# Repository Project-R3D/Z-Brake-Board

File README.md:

# Lulzbot Z Motor Automatic Brake

The [original design files](/Original_Lulz_Design/) contained within this repository were backed up from http://devel.lulzbot.com/electronics/dolores/ on Sept 8, 2021.
In case that gets taken down as well, please see this [archive.org](https://web.archive.org/web/20200216141835/http://devel.lulzbot.com/electronics/dolores/) backup as well.

This repository acts as a backup to that original design (which was sadly removed from all other Lulzbot servers) while complying with the original `CC BY SA 4.0` AND `GPL v3` license.

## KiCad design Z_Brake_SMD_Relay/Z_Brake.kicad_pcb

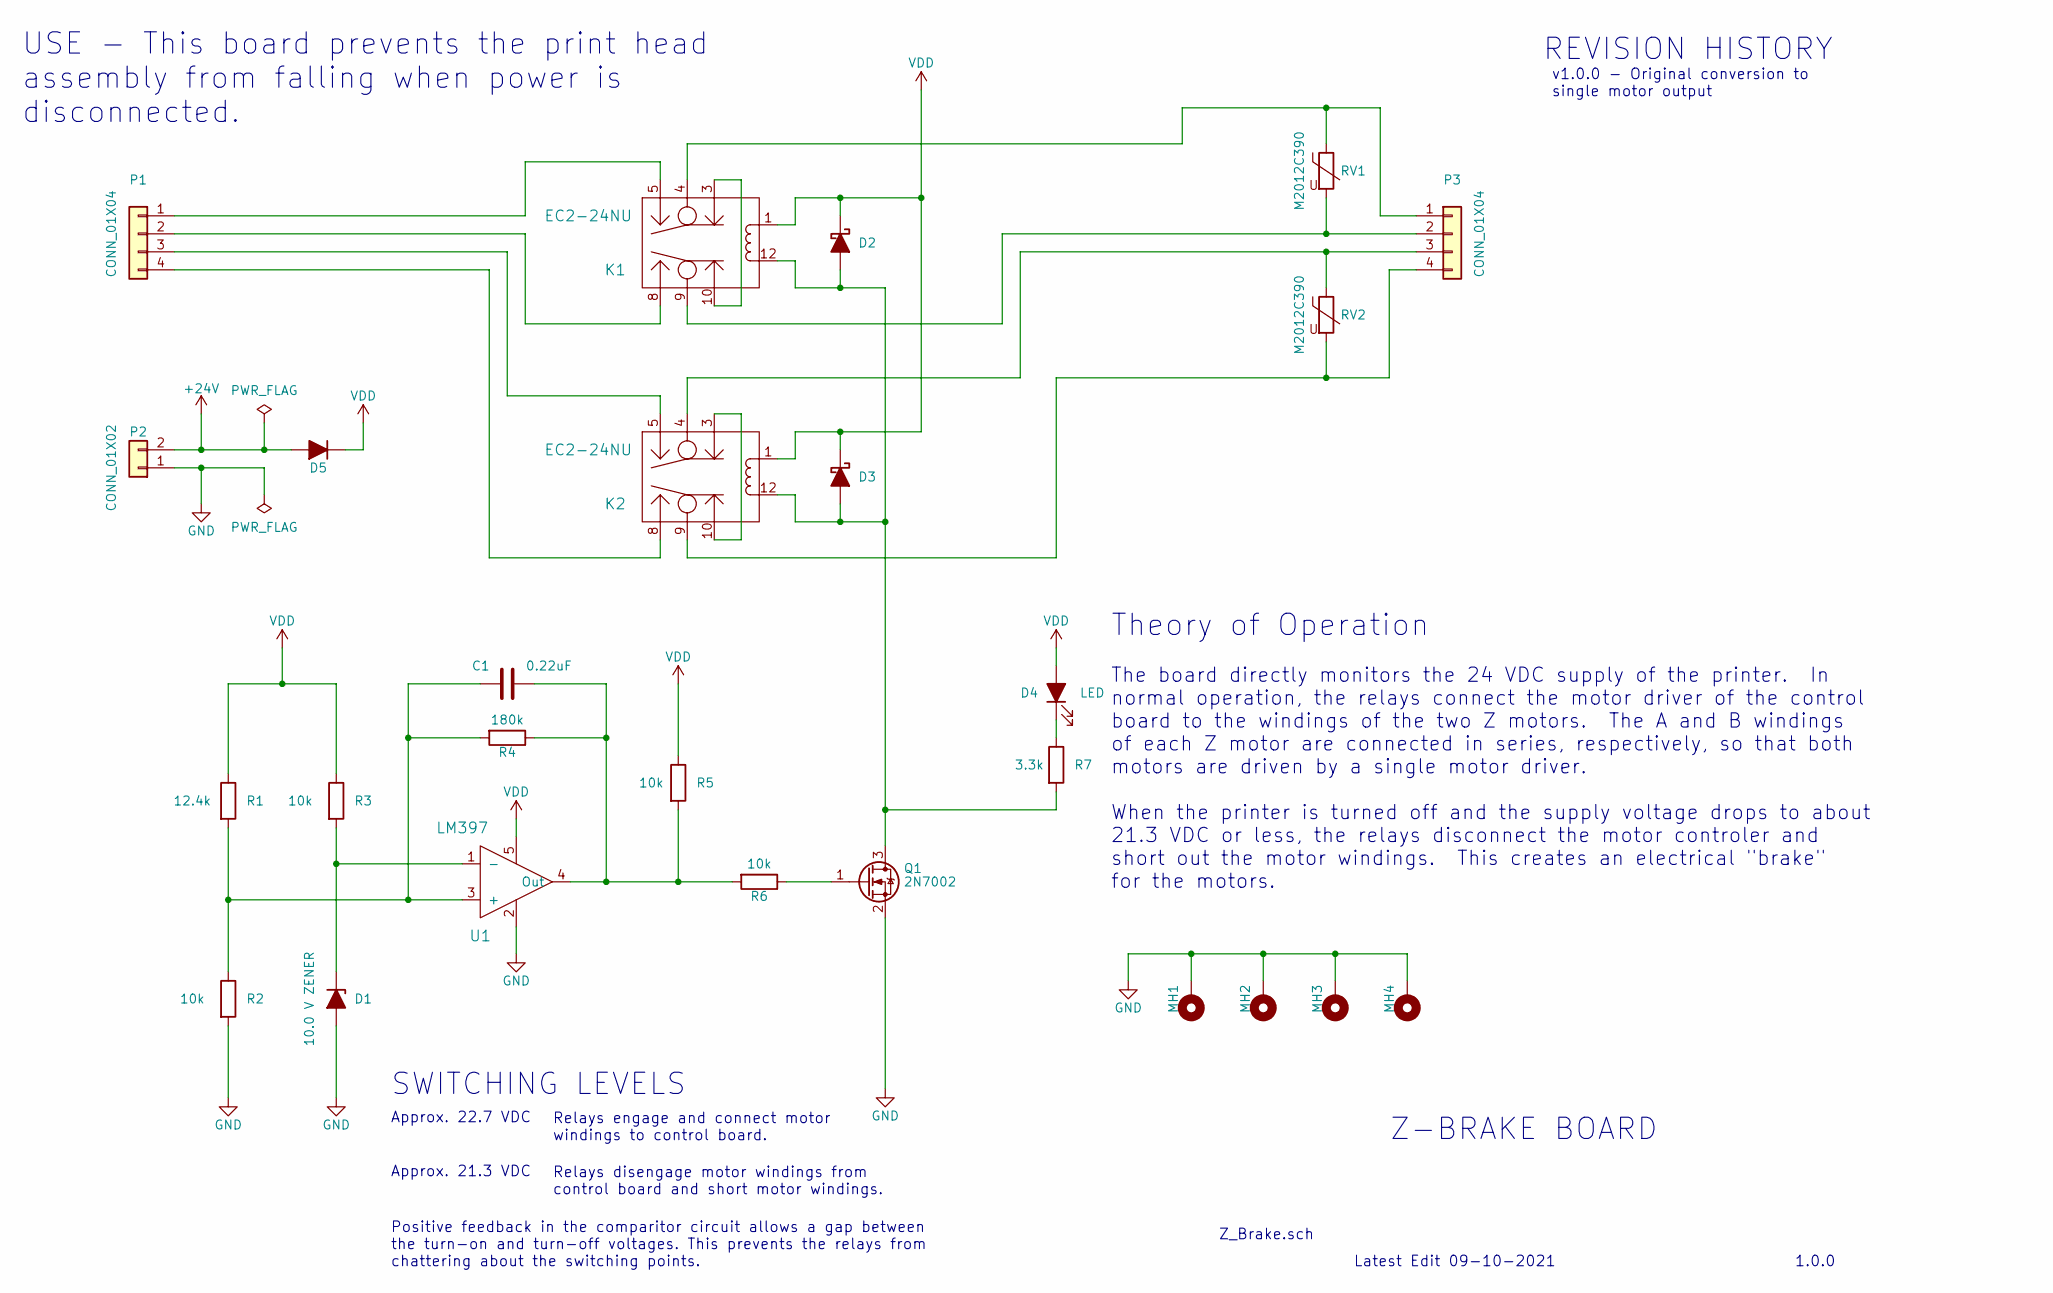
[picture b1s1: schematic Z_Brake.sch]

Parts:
C1: 0.22uF; C_0603_1608Metric_Pad1.08x0.95mm_HandSolder; MPN CL10B224KB8VPNC
D1: 10.0 V ZENER; D_SMA_Handsoldering; MPN SMAZ10-13-F
D2, D3: D_Schottky_ALT; D_SOD-123; MPN BAT48ZFILM
D4: LED; LED_0603_1608Metric_Pad1.05x0.95mm_HandSolder; MPN LTST-C190YKT
D5: D_ALT; D_SMA_Handsoldering; MPN CDBA340-HF
K1, K2: EC2-24NU; Relay_DPDT_Kemet_EE2_NU; MPN EC2-24NU
MH1, MH2, MH3, MH4: CONN_01X01; MountingHole_2.5mm_Pad
P1, P3: CONN_01X04; Molex-70543-0038-0-0-MFG; MPN 0705430003
P2: CONN_01X02; MOLEX_0705430001; MPN 0705430001
Q1: 2N7002; SOT-23_Handsoldering; MPN 2N7002 TR PBFREE
R1: 12.4k; R_0603_1608Metric_Pad0.98x0.95mm_HandSolder; MPN RC0603FR-0712K4L
R2, R3, R5, R6: 10k; R_0603_1608Metric_Pad0.98x0.95mm_HandSolder; MPN RC0603FR-0710KL
R4: 180k; R_0603_1608Metric_Pad0.98x0.95mm_HandSolder; MPN RC0603FR-07180KL
R7: 3.3k; R_0603_1608Metric_Pad0.98x0.95mm_HandSolder; MPN RC0603FR-073K3L
RV1, RV2: M2012C390; R_0805_2012Metric_Pad1.20x1.40mm_HandSolder; MPN AVR-M2012C390KT6AB
U1: LM397; SOT-23-5_HandSoldering; MPN LM397MF/NOPB

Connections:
+24V: D5.2 (A), P2.2
GND: D1.2 (A), MH1.1, MH2.1, MH3.1, MH4.1, P2.1, Q1.2 (S), R2.2, U1.2
unnamed: C1.1, R4.1, R5.2, R6.2, U1.4 (Out)
unnamed: C1.2, R1.2, R2.1, R4.2, U1.3 (+)
unnamed: D1.1 (K), R3.2, U1.1 (-)
unnamed: D2.2 (A), D3.2 (A), K1.12, K2.12, Q1.3 (D), R7.2
unnamed: D4.1 (K), R7.1
unnamed: K1.4, P3.1, RV1.1
unnamed: K1.5, P1.1
unnamed: K1.8, P1.2
unnamed: K1.9, P3.2, RV1.2
unnamed: K1.3, K1.10
unnamed: K2.4, P3.3, RV2.1
unnamed: K2.5, P1.3
unnamed: K2.8, P1.4
unnamed: K2.9, P3.4, RV2.2
unnamed: K2.3, K2.10
unnamed: Q1.1 (G), R6.1
VDD: D2.1 (K), D3.1 (K), D4.2 (A), D5.1 (K), K1.1, K2.1, R1.1, R3.1, R5.1, U1.5

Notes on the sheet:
Z-BRAKE BOARD
Z_Brake.sch
Latest Edit 09-10-2021
REVISION HISTORY
Approx. 22.7 VDC
SWITCHING LEVELS
Approx. 21.3 VDC
Relays engage and connect motor windings to control board.
Relays disengage motor windings from control board and short motor windings.
Theory of Operation
The board directly monitors the 24 VDC supply of the printer. In normal operation, the relays connect the motor driver of the control board to the windings of the two Z motors. The A and B windings of each Z motor are connected in series, respectively, so that both motors are driven by a single mot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
Positive feedback in the comparitor circuit allows a gap between the turn-on and turn-off voltages. This prevents the relays from chattering about the switching points.
USE - This board prevents the print head assembly from falling when power is disconnected.
1.0.0
v1.0.0 - Original conversion to single motor output

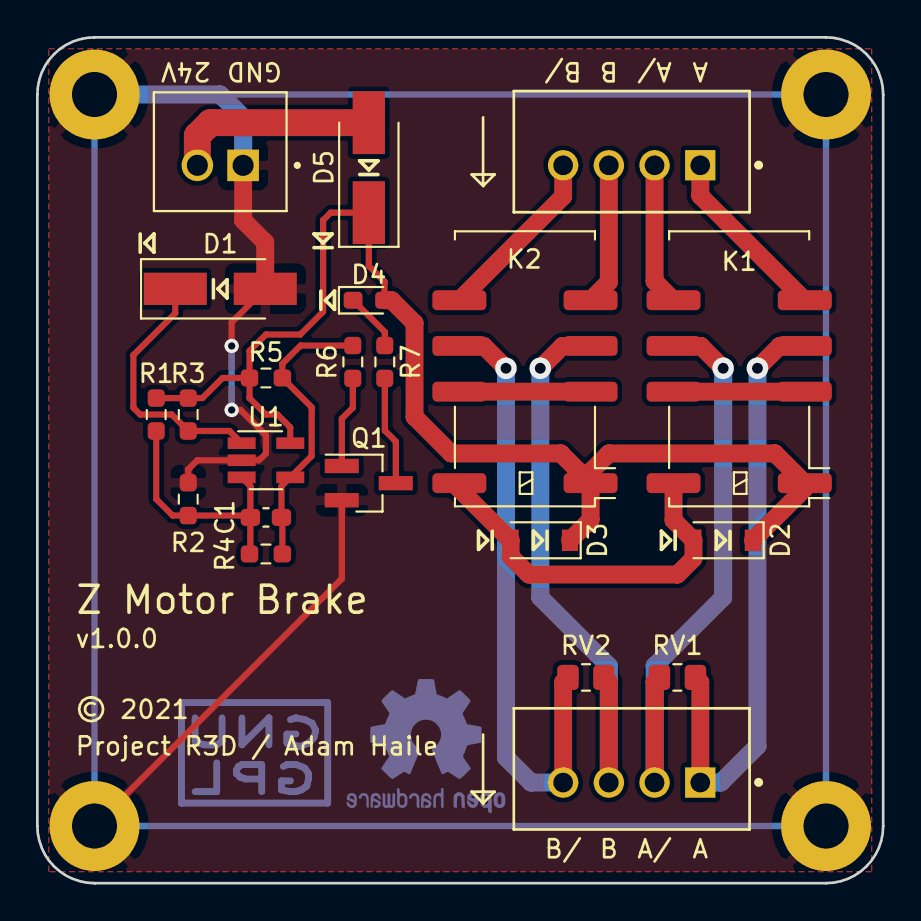
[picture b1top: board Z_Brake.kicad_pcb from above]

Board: 2 copper layers, 47.0 x 47.0 mm, 26 parts (0 on the bottom side), 19 nets.

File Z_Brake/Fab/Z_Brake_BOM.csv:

Qty,Reference(s),MPN,Manufacturer,Primary Supplier,Supplier PN
1,C1,CL10B224KB8VPNC,Samsung,Digikey,1276-6600-1-ND
1,D1,SMAZ10-13-F,Diodes Incorporated,Digikey,SMAZ10-FDICT-ND
2,"D2, D3",BAT48ZFILM,STMicroelectronics,Digikey,497-5712-1-ND
1,D4,LTST-C190YKT,Lite-On Inc.,Digikey,160-1184-1-ND
1,D5,CDBA340-HF,Comchip Technology,Digikey,641-1748-1-ND
2,"K1, K2",EC2-24NU,Kemet,Digikey,399-11037-5-ND
2,"P1, P3",705430003,Molex,Digikey,WM4802-ND
1,P2,705430001,Molex,Digikey,WM4800-ND
1,Q1,2N7002 TR PBFREE,Central Semiconductor Corp,Digikey,1514-2N7002TRPBFREECT-ND
1,R1,RC0603FR-0712K4L,YAGEO,Digikey,311-12.4KHRCT-ND
4,"R2, R3, R5, R6",RC0603FR-0710KL,YAGEO,Digikey,311-10.0KHRCT-ND
1,R4,RC0603FR-07180KL,YAGEO,Digikey,311-180KHRCT-ND
1,R7,RC0603FR-073K3L,YAGEO,Digikey,311-3.30KHRCT-ND
2,"RV1, RV2",AVR-M2012C390KT6AB,TDK,Digikey,445-2549-1-ND
1,U1,LM397MF/NOPB,TI,Digikey,LM397MF/NOPBCT-ND

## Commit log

2021-09-09 Initial backup
2021-09-09 Start on conversion to new KiCAD
2021-09-09 No more rescue files needed
2021-09-09 Added supplier part numbers for all
2021-09-09 Converted to single motor output
2021-09-09 Starting on PCB layout
2021-09-10 Final PCB
2021-09-10 Add fab files
2021-10-07 JLCPCB pos file
2021-10-31 Added smt relay version

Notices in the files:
Z_Brake_SMD_Relay/Z_Brake.kicad_pcb:
© 2021
